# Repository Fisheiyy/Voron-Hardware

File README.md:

# Voron-Hardware
Cool Hardware designed by the Voron Design group

| Project                    |      Overview                                                                       |
|----------------------------|-------------------------------------------------------------------------------------|
| Afterburner_Toolhead_PCB   | Breakout PCB for the Afterburner toolhead                                           |
| Daylight on a Stick        | LED PCB to illuminate your printer                                                  |
| Hall_Effect_XY_Endstop     | Replacement for mechanical endstop switches with an adjustable magnetic endstop PCB |
| Klipper_Expander           | Standalone MCU for use with Klipper with various inputs and outputs                 |
| Microswitch_Endstop        | PCB for mechanical endstop switches                                                 |
| Microswitch_Z_Endstop      | PCB for mechanical Z endstop switches                                               |
| Nano_Display               | Adapts an Arduino Nano to the RepRap standard 2 2x5pin IDC Connectors               |
| PT100Stick                 | PT100 board in StepStick format                                                     |
| SKR-Mini_Screen_Adaptor    | PCB to connect a 2 2x5 IDC cable screen to an SKR Mini E3 V1.2/2.0                  |
| STM32_Mini12864            | A standalone MCU for use with Klipper to drive a FYSETC Mini 12864 Display          |
| Stealthburner_Toolhead_PCB | Breakout PCB for the Afterburner toolhead                                           |
| Taco_Raven                 | 3D Printer controller with 8 integrated stepper drivers for use with Klipper        |
| V0-Umbilical               | Set of two PCBs for use with the V0.1 to make wiring easier and more modular        |
| V0_Display                 | Small Form Factor Display with OLED, Rotary Encoder or Buttons and Neopixel LED     |
| V0_Display_RP2040	         | Derivitive of V0 Display to use RP2040 over STM32                                   |
| V0_Micro_Display           | Micro Form Factor Display with OLED, Clickable D-pad and Neopixel LED               |
| V0_PCB_Mod                 | V0 Mod by JNP                                                                       |
| V0_Simple_Display          | V0 Simple Display is a remix of the V0 Display that doesnt need an STM32 MCU        |

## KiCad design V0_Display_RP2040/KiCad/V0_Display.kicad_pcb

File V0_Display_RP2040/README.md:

# RP2040 V0 Display #

[iBOM](http://htmlpreview.github.io/?https://github.com/Fisheiyy/RP2040_V0_Display/blob/master/KiCad/ibom.html)
### Derived from [Timmit99's V0 Display](https://github.com/VoronDesign/Voron-Hardware/tree/master/V0_Display)
### Sponsored by Provok3d.com & Lab4450.com

## The board has: ##
 - RP2040 MCU with 12MHz Crystal
 - SWD header for easy debugging (not populated by default)
 - USB C port
 - I2C Screen connections for  1.3" display with jumpers on back for slecting which pins (1 or 2) are power and ground
 - EN11-style click encoder support
 - Reset/kill button
 - 3 GPIO pin header
 - 1 on-board Neopixel with data line broken out for expansion

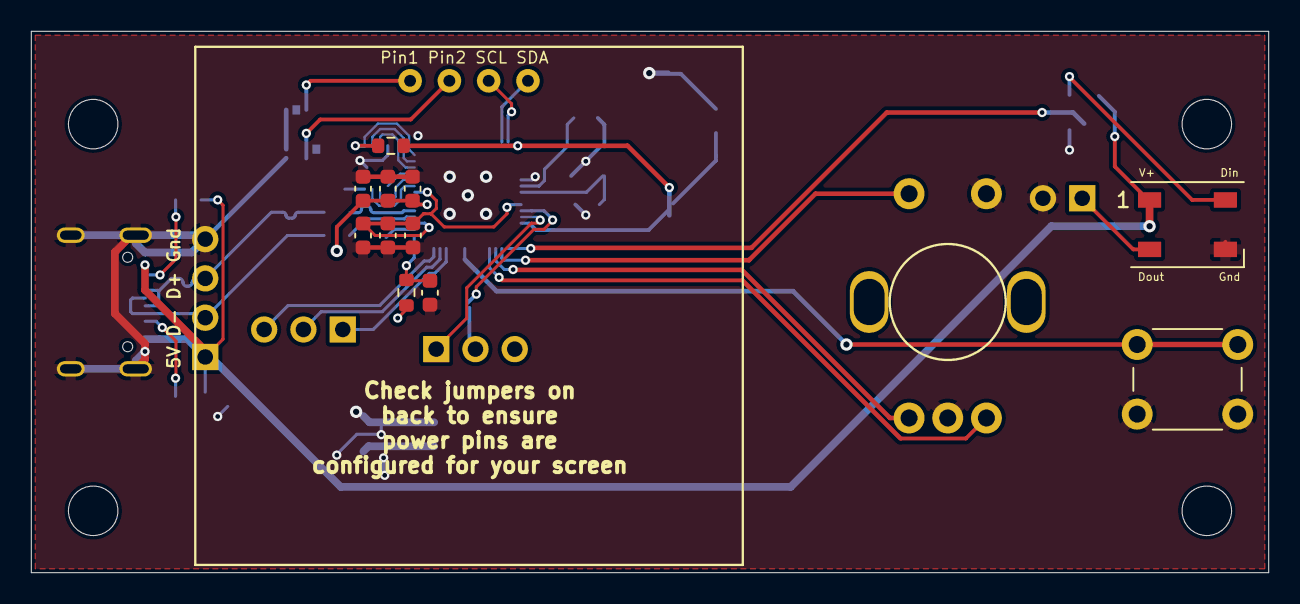
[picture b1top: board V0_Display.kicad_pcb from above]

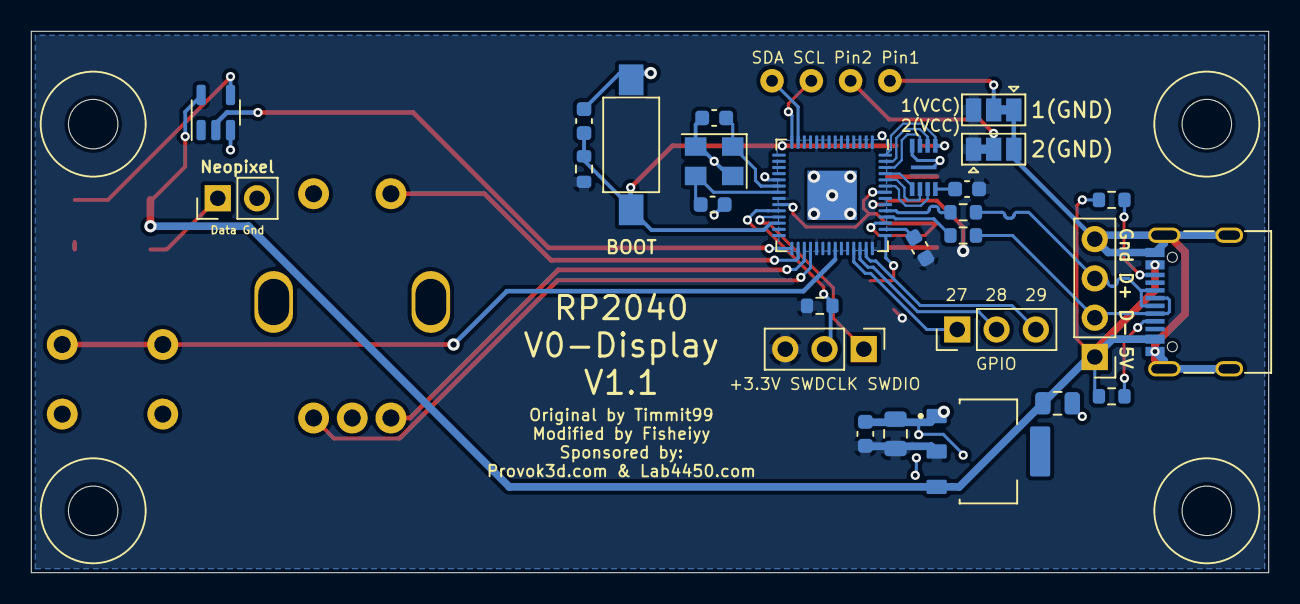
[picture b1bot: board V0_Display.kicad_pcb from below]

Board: 2 copper layers, 80.0 x 35.0 mm, 44 parts (27 on the bottom side), 38 nets.

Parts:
C1, C3: 22uF; C_0805_2012Metric
C2, C4, C6, C8, C9, C12, C13, C14: 0.1uF; C_0603_1608Metric
C5, C15: 12pF; C_0603_1608Metric
C7, C10, C11: 2.2uF; C_0603_1608Metric
D1: WS2812B; LED_WS2812B_PLCC4_5.0x5.0mm_P3.2mm
H1, H2, H3, H4: MountingHole; MountingHole_3.2mm_M3
J1: GPIO; PinHeader_1x03_P2.54mm_Vertical
J2: I2C Header; 1pt3in_OLED
J3: SWD; PinHeader_1x03_P2.54mm_Vertical
J4: GT-USB-7010ASV; USB_C_Receptacle_G-Switch_GT-USB-7010ASV
J5: USB_Header; PinHeader_1x04_P2.54mm_Vertical
J6: Neopixel; PinHeader_1x02_P2.54mm_Vertical
JP1: Pin2; SolderJumper-3_P1.3mm_Bridged12_Pad1.0x1.5mm
JP2: Pin1; SolderJumper-3_P1.3mm_Bridged12_Pad1.0x1.5mm
JP3: RUN; SW_SPST_FSMSM
R1, R3, R6, R8: 10K; R_0603_1608Metric
R2: 1K; R_0603_1608Metric
R4, R5: 27R; R_0603_1608Metric
R7: 200R; R_0603_1608Metric
SW1: Kill_SW; SW_PUSH_6mm
SW2: Rotary_Enc; EN11_Encoder
U1: AMS1117-3.3
U2: W25Q16JVUXIQ
U3: 74LVC1G17; SOT-23-5
U4: RP2040; QFN-56-1EP_7x7mm_P0.4mm_EP3.2x3.2mm
Y1: 12MHz; Oscillator_SMD_SeikoEpson_SG8002CE-4Pin_3.2x2.5mm

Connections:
+1V1: C7.1, C8.1, C9.1, U4.23 (DVDD), U4.45 (VREG_VOUT), U4.50 (DVDD)
+3.3V: C1.1, C2.1, C4.2, C10.1, C12.1, C13.1, C14.1, J3.3, JP1.1 (A), JP2.3 (B), R3.2, R6.2, R7.2, U1.2 (VOUT), U4.1 (IOVDD), U4.10 (IOVDD), U4.22 (IOVDD), U4.33 (IOVDD), U4.42 (IOVDD), U4.48 (USB_VDD), U4.49 (IOVDD)
/D+: R4.2, U4.47 (USB_DP)
/D-: R5.1, U4.46 (USB_DM)
CLK: U2.6 (CLK), U4.52 (QSPI_SCLK)
CS: R2.1, U2.1 (~CS), U4.56 (QSPI_SS)
D27+: J4.A6 (D+), J4.B6 (D+), J5.3, R4.1
D27-: J4.A7 (D-), J4.B7 (D-), J5.2, R5.2
Enc_A: SW2.A, U4.31 (GPIO20)
Enc_B: SW2.B, U4.32 (GPIO21)
Enc_SW: SW2.S1, U4.30 (GPIO19)
F_PD: C6.2, JP3.2 (B), R2.2, R6.1, U4.26 (RUN)
GND: C1.2, C2.2, C3.2, C5.2, C6.1, C7.2, C8.2, C9.2, C11.2, C12.2, C13.2, C14.2, C15.2, D1.3 (VSS), J4.A1 (GND), J4.A12 (GND), J4.B1 (GND), J4.B12 (GND), J4.S1 (SHIELD), J5.4, J6.2, JP1.3 (B), JP2.1 (A), JP3.1 (A), SW1.2 (B), SW2.C, SW2.S2, U1.1 (ADJ/GND), U2.4 (GND), U2.9 (EP), U3.3 (GND), U4.19 (TESTEN), U4.57 (GND), Y1.2, Y1.4
GPIO27: J1.1, U4.39 (GPIO27_ADC1)
GPIO28: J1.2, U4.40 (GPIO28_ADC2)
GPIO29: J1.3, U4.41 (GPIO29_ADC3)
Kill: SW1.1 (A), U4.36 (GPIO24)
Neopixel: U3.2, U4.29 (GPIO18)
unnamed: D1.4 (DIN), U3.4
unnamed: D1.2 (DOUT), J6.1
unnamed: J4.A5 (CC1), R1.1
unnamed: J4.B5 (CC2), R8.1
unnamed: C4.1, U2.8 (VCC)
unnamed: C11.1, R7.1, U4.43 (ADC_AVDD)
unnamed: C10.2, U4.44 (VREG_IN)
unnamed: C5.1, U4.20 (XIN), Y1.1
unnamed: C15.1, U4.21 (XOUT), Y1.3
Pin1: J2.1, JP2.2 (C)
Pin2: J2.2, JP1.2 (C)
SCL: J2.3, U4.14 (GPIO11)
SD0: U2.5 (DI_(IO0)), U4.53 (QSPI_SD0)
SD1: U2.2 (DO_(IO1)), U4.55 (QSPI_SD1)
SD2: U2.3 (~WP_(IO2)), U4.54 (QSPI_SD2)
SD3: U2.7 (~HOLD_OR_RESET_(IO3)), U4.51 (QSPI_SD3)
SDA: J2.4, U4.13 (GPIO10)
SWDCLK: J3.2, R3.1, U4.24 (SWCLK)
SWDIO: J3.1, U4.25 (SWD)
VBUS: C3.1, D1.1 (VDD), J4.A4 (VBUS), J4.A9 (VBUS), J4.B4 (VBUS), J4.B9 (VBUS), J5.1, R1.2, R8.2, U1.3 (VIN), U3.5 (VCC)

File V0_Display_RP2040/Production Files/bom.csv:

Designator,Footprint,Quantity,Value,LCSC Part #
"C1, C3",0805,2,22uF,C2859526
"C10, C11, C7",0603,3,2.2uF,C71000
"C12, C13, C14, C2, C4, C6, C8, C9",0603,8,0.1uF,C30926
"C15, C5",0603,2,12pF,C107034
D1,LED_WS2812B_PLCC4_5.0x5.0mm_P3.2mm,1,WS2812B,C2843785
"H1, H2, H3, H4",MountingHole_3.2mm_M3,4,MountingHole,
J1,PinHeader_1x03_P2.54mm_Vertical,1,GPIO,C429954
J2,1pt3in_OLED,1,I2C Header,N/A
J3,PinHeader_1x03_P2.54mm_Vertical,1,SWD,C429954
J4,USB_C_Receptacle_G-Switch_GT-USB-7010ASV,1,GT-USB-7010ASV,C2988369
J5,PinHeader_1x04_P2.54mm_Vertical,1,USB_Header,
J6,PinHeader_1x02_P2.54mm_Vertical,1,Neopixel,C2894925
JP1,SolderJumper-3_P1.3mm_Bridged12_Pad1.0x1.5mm,1,Pin2,N/A
JP2,SolderJumper-3_P1.3mm_Bridged12_Pad1.0x1.5mm,1,Pin1,N/A
JP3,SW_SPST_FSMSM,1,RUN,C118141
"R1, R3, R6, R8",0603,4,10K,C304415
R2,0603,1,1K,C110774
"R4, R5",0603,2,27R,C861276
R7,0603,1,200R,C8218
SW1,SW_PUSH_6mm,1,Kill_SW,C455090
SW2,EN11_Encoder,1,Rotary_Enc,N/A
U1,AMS1117-3.3,1,AMS1117-3.3,C6186
U2,W25Q16JVUXIQ,1,W25Q16JVUXIQ,C2843335
U3,SOT-23-5,1,74LVC1G17,C6076
U4,QFN-56-1EP_7x7mm_P0.4mm_EP3.2x3.2mm,1,RP2040,C2040
Y1,Oscillator_SMD_SeikoEpson_SG8002CE-4Pin_3.2x2.5mm,1,12MHz,C654949

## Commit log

2023-03-04 Add V0_Display_RP2040
2023-03-04 Update Images
2023-03-05 Fix Footprints
2023-03-22 Update Files
    New 3.3V Regulator
    "Fixed" Neopixel Level Shifter
2023-03-25 Rev 1.1
    Fix Vreg-Out Problem
    Change to AMS1117-3.3
    22uF Input Capacitor on VBUS (5V IN)
